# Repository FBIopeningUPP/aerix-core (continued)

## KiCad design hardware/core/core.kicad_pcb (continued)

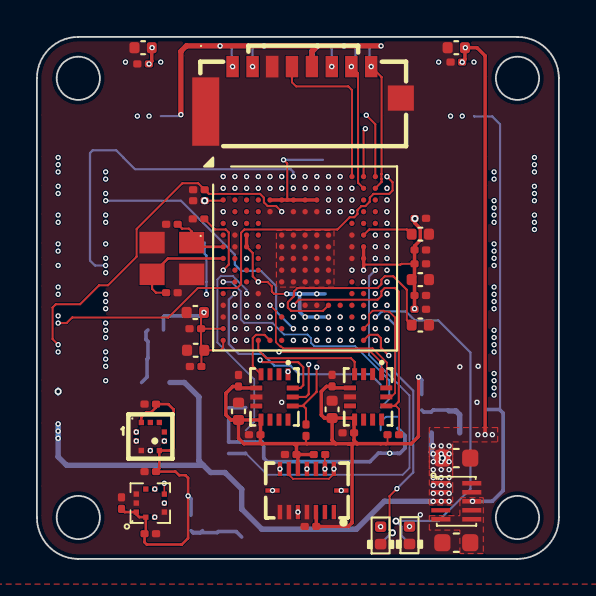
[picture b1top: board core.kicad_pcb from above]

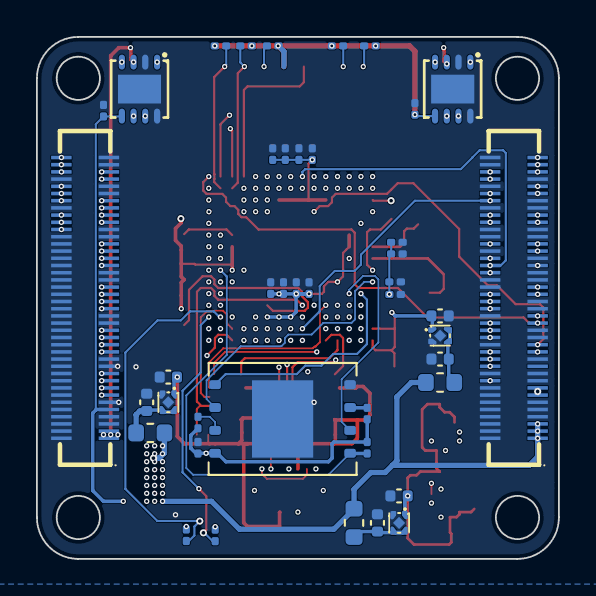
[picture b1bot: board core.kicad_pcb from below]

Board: 8 copper layers, 29.0 x 29.0 mm, 91 parts (42 on the bottom side), 122 nets.

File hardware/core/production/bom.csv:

Designator,Footprint,Quantity,Value,LCSC Part #
"C1, C10, C11, C12, C13, C14, C15, C2, C20, C22, C24, C27, C28, C3, C30, C31, C33, C34, C35, C36, C37, C38, C4, C40, C41, C43, C44, C46, C47, C48, C5, C6, C7, C8, C9",0201,35,100nF,
"C16, C17, C18",0201,3,4.7uF,
"C19, C21, C23, C51, C52, C53, C54, C55, C56",0402,9,1uF,
"C25, C26, C29, C32",0402,4,2.2uF,
"C42, C45",0402,2,4.7uF,
C49,0603,1,10uF,
C50,0603,1,22uF,
CARD1,TF-SMD_TF-021B-H265,1,TF-021B-H265,C498185
"CN1, CN2",CONN-SMD_DF40C-80DS-0.4V-51,2,DF40C-80DS-0.4V,C312960
"FB1, FB2, FB3",0603,3,600,
"LED1, LED2",0402,2,LED_0402,
"R1, R2, R3, R4, R5, R6, R7",0201,7,10k,
"R10, R11, R12, R8, R9",0201,5,47k,
"R13, R14",0201,2,1k,
U1,UFBGA-201_10x10mm_Layout15x15_P0.65mm,1,STM32H743IIKx,
"U10, U9",TDFN-8_L3.0-W3.0-P0.65-BL-EP,2,TCAN1044AVDRBRQ1,C3234119
"U11, U12, U13",X2SON-4_L1.0-W1.0-P0.65-TL-EP,3,TPS7A2033PDQNR,C2871641
U14,USIP-10_L2.5-W2.0-P0.50-BL,1,TPSM82822SILR,C5219367
U2,LGA-14_L3.0-W2.5-P0.50-TL,1,IIM-42653,C30724128
U3,LGA-14_L3.0-W2.5-P0.50-TL,1,ICM-45686,C22459454
U4,LGA-16_L4.5-W3.0-P0.50-BL,1,BMI088,C194919
U5,LGA-10_L2.0-W2.0-P0.50-BL,1,BMP390_C5124834,C5124834
U6,LGA-10_L2.0-W2.0-P0.50-TL_ICP-20100,1,ICP-20100,C5343527
U7,WSON-8-1EP_8x6mm_P1.27mm_EP3.4x4.3mm,1,W25Q128JVE,
X1,CRYSTAL-SMD_4P-L3.2-W2.5-BL-1,1,ABM8W-16.0000MHZ-8-D1X-T3,C193746
